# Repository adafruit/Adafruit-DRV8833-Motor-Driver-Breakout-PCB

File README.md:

## Adafruit DRV8833 Motor Driver Breakout PCB

<a href="http://www.adafruit.com/products/3297"><br/>
Click here to purchase one from the Adafruit shop</a>

PCB files for the Adafurit DRV8833 Motor Driver Breakout. Format is EagleCAD schematic and board layout
* https://www.adafruit.com/product/3297

### DESCRIPTION
Spin two DC motors or step one bi-polar or uni-polar stepper with up to 1.2A per channel using the DRV8833. This motor driver chip is a nice alternative to the TB6612 driver. Like that chip, you get 2 full H-bridges, but this chip is better for low voltage uses (can run from 2.7V up to 10.8V motor power) and has built in current limiting capability. We set it up for 1A current limiting so you don't get more than 2A per chip, but you can also disable the current limiting, or change it to a different limit!

We solder on DRV8833 onto a breakout board for you here, with a polarity protection FET on the motor voltage input. Each breakout chip contains two full H-bridges (four half H-bridges). That means you can drive two DC motors bi-directionally, or one stepper motor. Just make sure they're good for about 1.2 Amp or less of current, since that's the limit of this chip. They do handle a peak of 2A but that's just for a short amount of time, if you turn off the current limiting we set. What we like most about this particular driver is that it comes with built in kick-back diodes internally so you dont have to worry about the inductive kick damaging your project or driver! You also don't have to worry as much about burning out the chip with overdriving since there is current limiting.

There's two digital inputs per H-bridge (one for each half of the bridge), you can PWM one of the inputs to control motor speed. Runs at 2.7V-10.8V logic/motor power. The motor voltage is the same as the logic voltage, but logic voltage from 2.7V or greater will work so no need to worry if you are powering the motors from 9V and using 3.3V logic. For higher voltages, check out the TB6612. For much higher voltages and currents check out the DRV8871!

### License

Adafruit invests time and resources providing this open source design, please support Adafruit and open-source hardware by purchasing products from [Adafruit.com](https://www.adafruit.com)!

Creative Commons Attribution, Share-Alike license, check license.txt for more information All text above must be included in any redistribution - 
See license.txt for more information.

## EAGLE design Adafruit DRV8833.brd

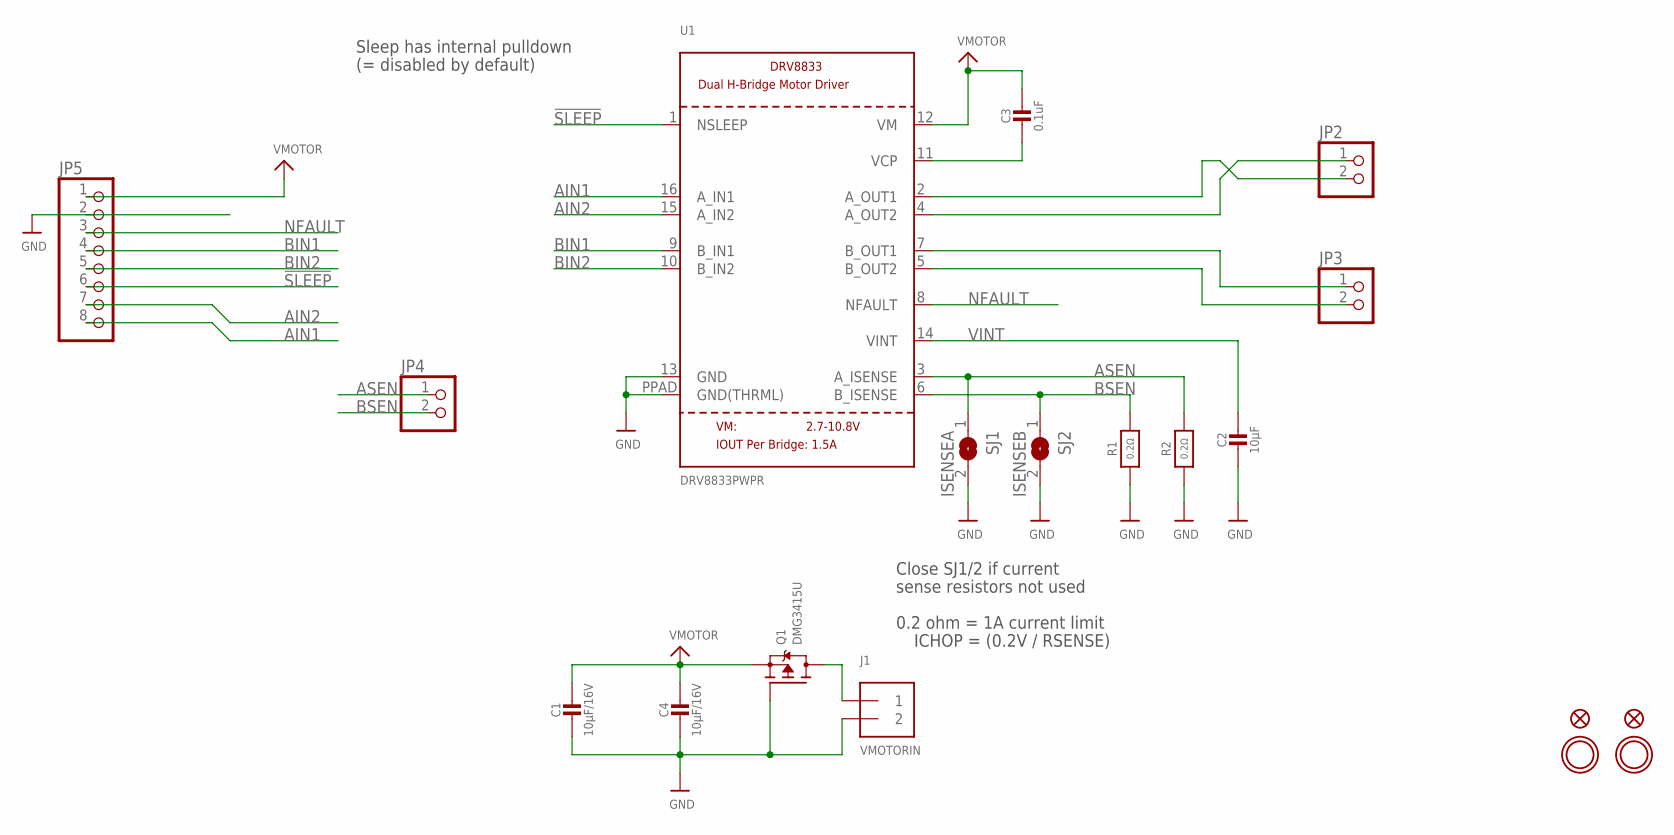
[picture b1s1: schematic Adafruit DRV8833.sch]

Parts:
C1, C4: 10µF/16V; 0805-NO
C2: 10µF; 0805-NO
C3: 0.1uF; 0805-NO
FID1, FID2: FIDUCIAL""; FIDUCIAL_1MM
J1: VMOTORIN; TERMBLOCK_1X2-3.5MM
JP2, JP3, JP4: HEADER-1X2ROUND; 1X02_ROUND
JP5: HEADER-1X870MIL; 1X08_ROUND_70
Q1: DMG3415U; SOT23-WIDE
R1, R2: 0.2Ω; _1206
SJ1: ISENSEA; SOLDERJUMPER_ARROW_NOPASTE
SJ2: ISENSEB; SOLDERJUMPER_ARROW_NOPASTE
U1: DRV8833PWPR; HTSSOP16
U$13, U$14: MOUNTINGHOLE2.5; MOUNTINGHOLE_2.5_PLATED

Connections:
!SLEEP: JP5.6, U1.1 (NSLEEP)
AIN1: JP5.8, U1.16 (A_IN1)
AIN2: JP5.7, U1.15 (A_IN2)
AOUT1: JP2.2, U1.2 (A_OUT1)
AOUT2: JP2.1, U1.4 (A_OUT2)
ASEN: JP4.1, R2.2, SJ1.1, U1.3 (A_ISENSE)
BIN1: JP5.4, U1.9 (B_IN1)
BIN2: JP5.5, U1.10 (B_IN2)
BOUT1: JP3.1, U1.7 (B_OUT1)
BOUT2: JP3.2, U1.5 (B_OUT2)
BSEN: JP4.2, R1.2, SJ2.1, U1.6 (B_ISENSE)
GND: C1.2, C2.2, C4.2, J1.2, JP5.2, Q1.1 (G), R1.1, R2.1, SJ1.2, SJ2.2, U1.13 (GND), U1.PPAD (GND(THRML))
unnamed: C3.2, U1.11 (VCP)
NFAULT: JP5.3, U1.8 (NFAULT)
PWRIN: J1.1, Q1.3 (D)
VINT: C2.1, U1.14 (VINT)
VMOTOR: C1.1, C3.1, C4.1, JP5.1, Q1.2 (S), U1.12 (VM)

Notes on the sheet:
Close SJ1/2 if current
sense resistors not used
0.2 ohm = 1A current limit
ICHOP = (0.2V / RSENSE)
Sleep has internal pulldown
(= disabled by default)

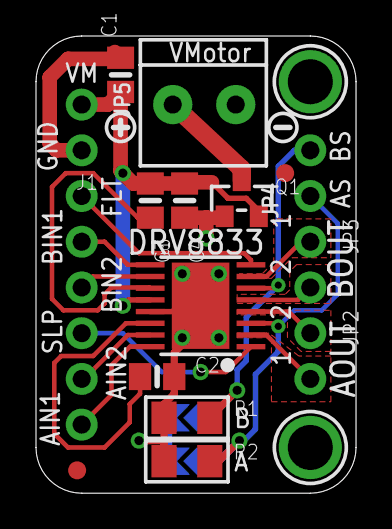
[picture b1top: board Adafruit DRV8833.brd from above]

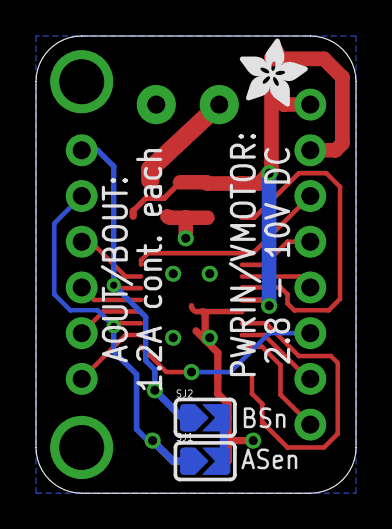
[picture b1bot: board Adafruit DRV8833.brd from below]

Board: 2 copper layers, 17.8 x 25.4 mm, 22 parts (3 on the bottom side), 17 nets.

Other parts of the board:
U$15: SYMBOL_PLUS
U$16: SYMBOL_MINUS
U$17: ADAFRUIT_3.5MM

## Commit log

2016-10-26 init
2016-10-26 neaten up
